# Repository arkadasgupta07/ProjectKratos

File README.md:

<p align="center">
  <!-- Replace the 'src' below with the actual path/link to your Project Kratos logo -->
  
</p>

<p align="center">
  <strong>~ Arka Dasgupta ~</strong><br>
  <strong>BITS Pilani, K. K. Birla Goa Campus</strong><br>
  <em>Aspiring to develop rovers by engineering their electronics, controls and automation subsystems.</em>
</p>

---

## ⚡ Core Engineering Domains

This repository primarily hosts my work in the domains of **Electronics, Controls and Automation**, aiming to build robust hardware and intelligent software stacks that drive our rovers across simulated and physical extraterrestrial terrains.

### 🔌 Electronics & Hardware
Focuses on the power, communication, and physical execution of the rover.
* **Power Distribution:** Custom-designed Power Distribution Boards (PDBs).
* **Embedded Systems:** Microcontroller programming and sensor integration.
* **Circuit Design:** Hardware schematics, PCB design, and component selection.
  
### 🤖 Automation & Controls
Focuses on making the rover intelligent and fully autonomous. 
* **Navigation Stack:** ROS/ROS2, Nav2, and SLAM for terrain mapping and path planning.
* **Computer Vision:** OpenCV and ArUCO marker detection for precise localization and object search.
* **Simulation:** Ground control stations and turtlebot/rover physics simulations in Gazebo.

---

## 📂 Repository Structure

Navigate through our project files below:

```text
ProjectKratos/
├── Documentation/            # Project reports, media, and track inductions
│   ├── Automation_Inductions/ # Automation track GUI, Nav2, and Vision demos
│   └── EnC_Inductions/        # Electronics & Communication documentation
├── Hardware/                 # PCB designs, schematics, and CAD files
├── src/                      # Robotics ROS packages & automation source code
└── README.md                 # You are here!

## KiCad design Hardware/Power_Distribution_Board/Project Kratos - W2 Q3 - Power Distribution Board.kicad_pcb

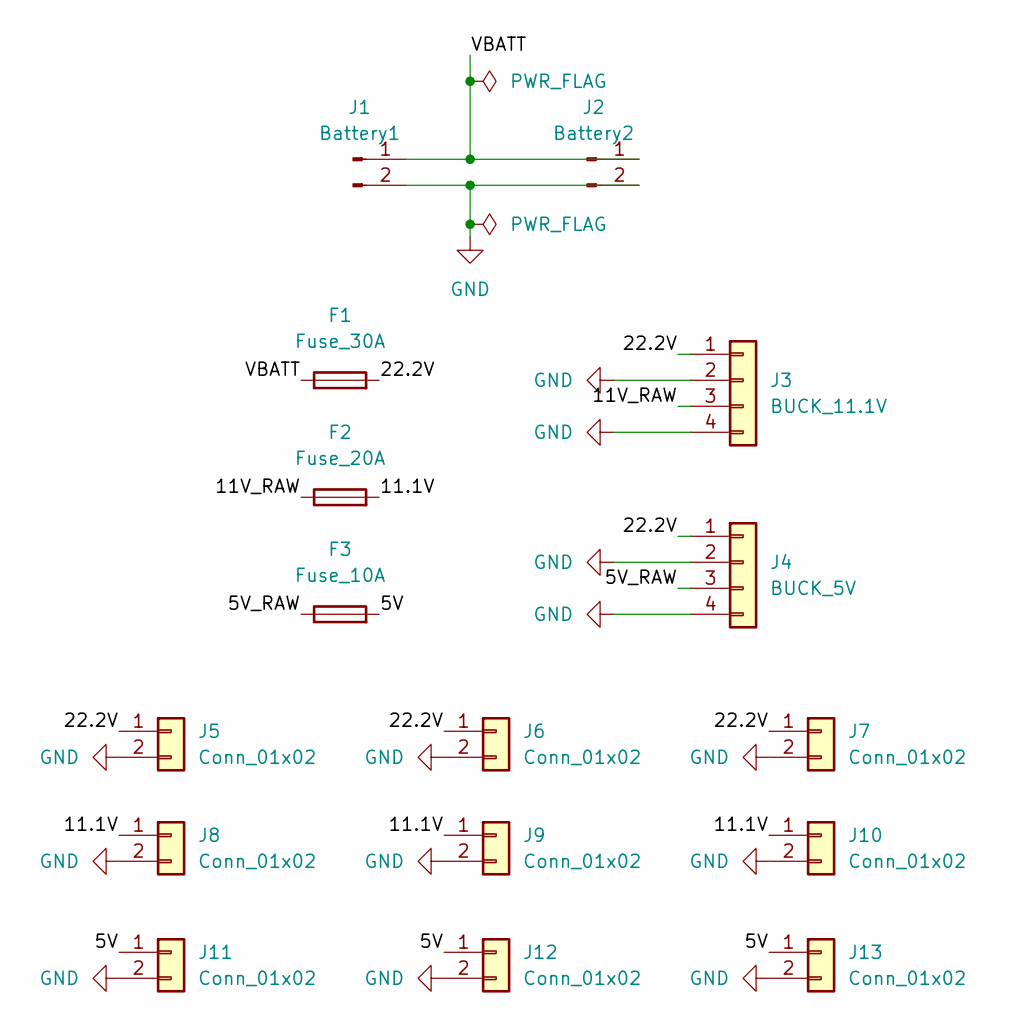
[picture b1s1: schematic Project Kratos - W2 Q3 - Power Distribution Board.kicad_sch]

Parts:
F1: Fuse_30A; FuseHolder_Blade_ATO_Littelfuse_FLR_178.6165
F2: Fuse_20A; FuseHolder_Blade_ATO_Littelfuse_FLR_178.6165
F3: Fuse_10A; FuseHolder_Blade_ATO_Littelfuse_FLR_178.6165
J1: Battery1; AMASS_XT60-F_1x02_P7.20mm_Vertical
J2: Battery2; AMASS_XT60-F_1x02_P7.20mm_Vertical
J3: BUCK_11.1V; PinHeader_1x04_P2.54mm_Vertical
J4: BUCK_5V; PinHeader_1x04_P2.54mm_Vertical
J5, J6, J7, J8, J9, J10: Conn_01x02; AMASS_XT60-M_1x02_P7.20mm_Vertical
J11, J12, J13: Conn_01x02; PinHeader_1x02_P2.54mm_Vertical

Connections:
/5V: F3.2, J11.1, J12.1, J13.1
/5V_RAW: F3.1, J4.3
/11.1V: F2.2, J8.1, J9.1, J10.1
/11V_RAW: F2.1, J3.3
/22.2V: F1.2, J3.1, J4.1, J5.1, J6.1, J7.1
/VBATT: F1.1, J1.1, J2.1
GND: J1.2, J2.2, J3.2, J3.4, J4.2, J4.4, J5.2, J6.2, J7.2, J8.2, J9.2, J10.2, J11.2, J12.2, J13.2

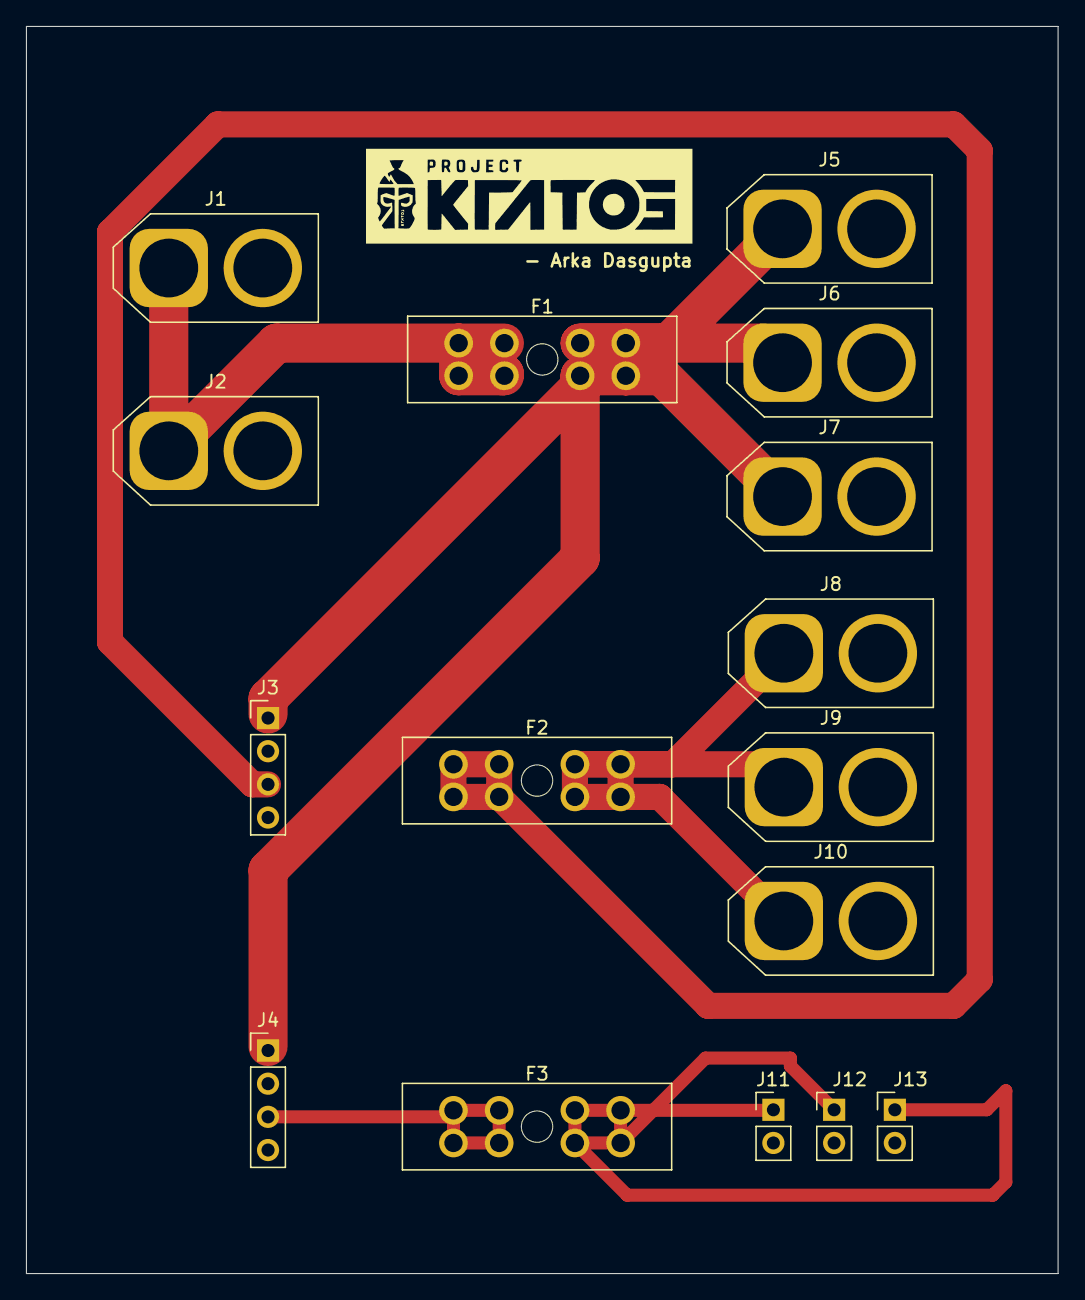
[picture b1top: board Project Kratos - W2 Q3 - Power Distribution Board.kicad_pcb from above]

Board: 2 copper layers, 79.0 x 95.5 mm, 16 parts (0 on the bottom side), 7 nets.

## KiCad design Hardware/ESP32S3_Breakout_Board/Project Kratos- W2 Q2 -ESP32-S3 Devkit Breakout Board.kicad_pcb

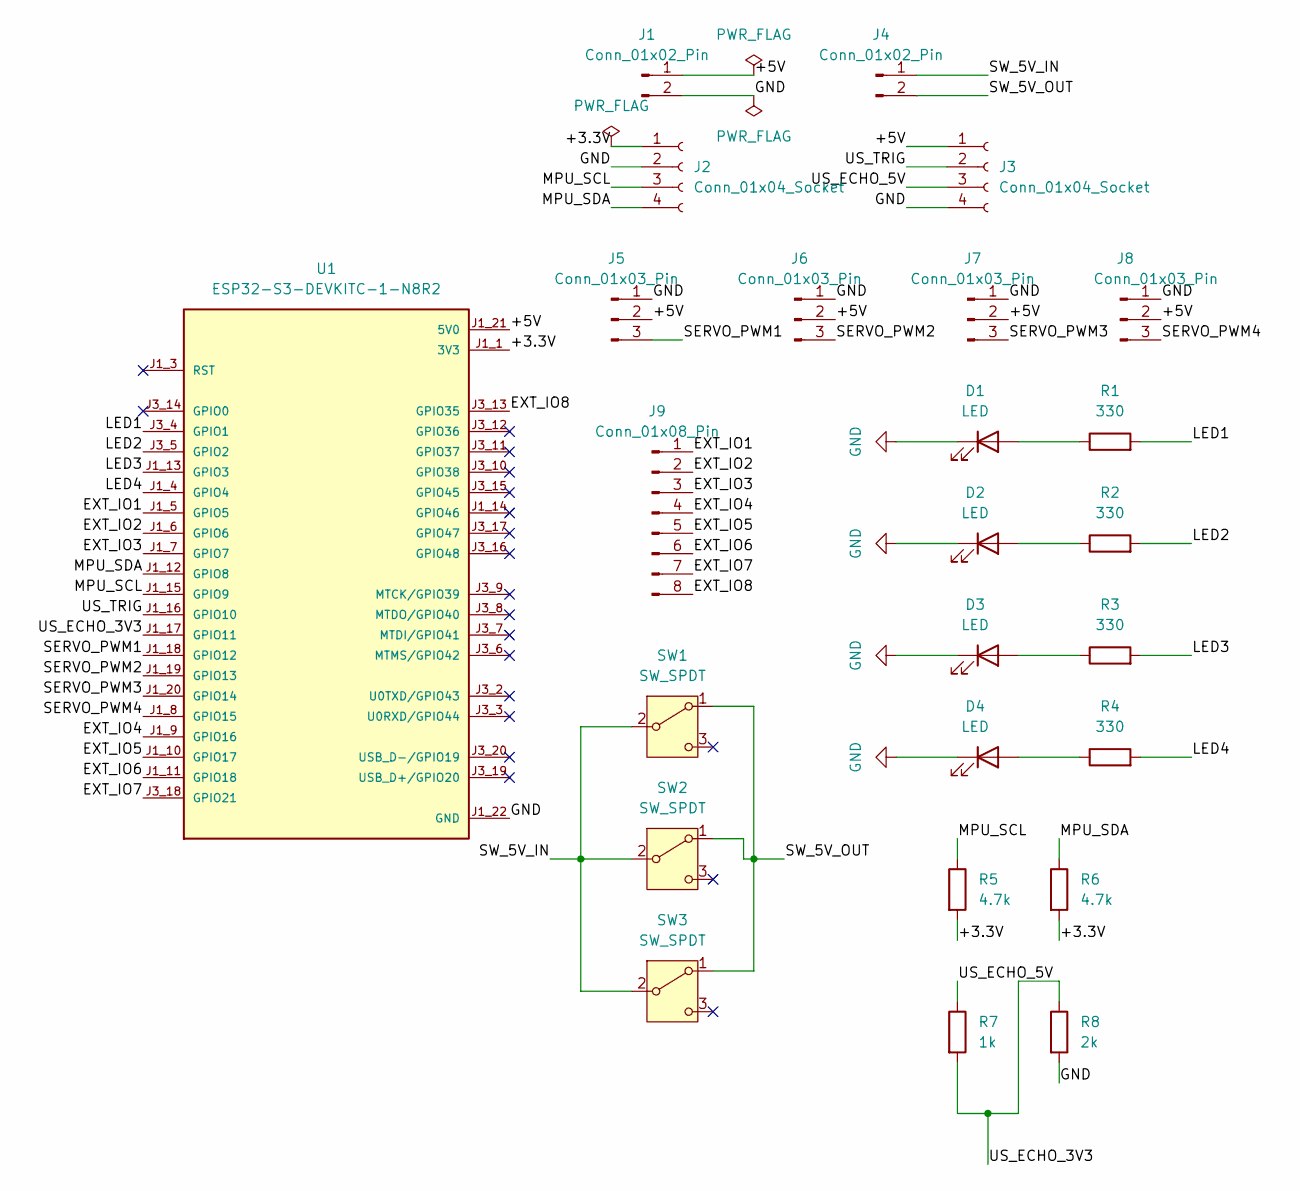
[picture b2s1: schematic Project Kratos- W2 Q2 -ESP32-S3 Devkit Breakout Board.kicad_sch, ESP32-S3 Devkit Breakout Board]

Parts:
D1, D2, D3, D4: LED; LED_D5.0mm
J1, J4: Conn_01x02_Pin; TerminalBlock_Phoenix_PT-1,5-2-3.5-H_1x02_P3.50mm_Horizontal
J2, J3: Conn_01x04_Socket; PinSocket_1x04_P2.54mm_Vertical
J5, J6, J7, J8: Conn_01x03_Pin; PinHeader_1x03_P2.54mm_Vertical
J9: Conn_01x08_Pin; PinHeader_1x08_P2.54mm_Vertical
R1, R2, R3, R4: 330; R_Axial_DIN0207_L6.3mm_D2.5mm_P7.62mm_Horizontal
R5, R6: 4.7k; R_Axial_DIN0207_L6.3mm_D2.5mm_P7.62mm_Horizontal
R7: 1k; R_Axial_DIN0207_L6.3mm_D2.5mm_P7.62mm_Horizontal
R8: 2k; R_Axial_DIN0207_L6.3mm_D2.5mm_P7.62mm_Horizontal
SW1, SW2, SW3: SW_SPDT; SW_Slide_SPDT_Straight_CK_OS102011MS2Q
U1: ESP32-S3-DEVKITC-1-N8R2; XCVR_ESP32-S3-DEVKITC-1-N8R2; PARTREV V1

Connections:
3V3: J2.1, R5.2, R6.2, U1.J1_1 (3V3), U1.J1_2 (3V3)
/+5V: J1.1, J3.1, J5.2, J6.2, J7.2, J8.2, U1.J1_21 (5V0)
/EXT_IO1: J9.1, U1.J1_5 (GPIO5)
/EXT_IO2: J9.2, U1.J1_6 (GPIO6)
/EXT_IO3: J9.3, U1.J1_7 (GPIO7)
/EXT_IO4: J9.4, U1.J1_9 (GPIO16)
/EXT_IO5: J9.5, U1.J1_10 (GPIO17)
/EXT_IO6: J9.6, U1.J1_11 (GPIO18)
/EXT_IO7: J9.7, U1.J3_18 (GPIO21)
/EXT_IO8: J9.8, U1.J3_13 (GPIO35)
/LED1: R1.2, U1.J3_4 (GPIO1)
/LED2: R2.2, U1.J3_5 (GPIO2)
/LED3: R3.2, U1.J1_13 (GPIO3)
/LED4: R4.2, U1.J1_4 (GPIO4)
/MPU_SCL: J2.3, R5.1, U1.J1_15 (GPIO9)
/MPU_SDA: J2.4, R6.1, U1.J1_12 (GPIO8)
/SERVO_PWM1: J5.3, U1.J1_18 (GPIO12)
/SERVO_PWM2: J6.3, U1.J1_19 (GPIO13)
/SERVO_PWM3: J7.3, U1.J1_20 (GPIO14)
/SERVO_PWM4: J8.3, U1.J1_8 (GPIO15)
/SW_5V_IN: J4.1, SW1.2 (B), SW2.2 (B), SW3.2 (B)
/SW_5V_OUT: J4.2, SW1.1 (A), SW2.1 (A), SW3.1 (A)
/US_ECHO_3V3: R7.2, R8.1, U1.J1_17 (GPIO11)
/US_ECHO_5V: J3.3, R7.1
/US_TRIG: J3.2, U1.J1_16 (GPIO10)
GND: D1.1 (K), D2.1 (K), D3.1 (K), D4.1 (K), J1.2, J2.2, J3.4, J5.1, J6.1, J7.1, J8.1, R8.2, U1.J1_22 (GND), U1.J3_1 (GND), U1.J3_21 (GND), U1.J3_22 (GND)
unnamed: D1.2 (A), R1.1
unnamed: D2.2 (A), R2.1
unnamed: D3.2 (A), R3.1
unnamed: D4.2 (A), R4.1

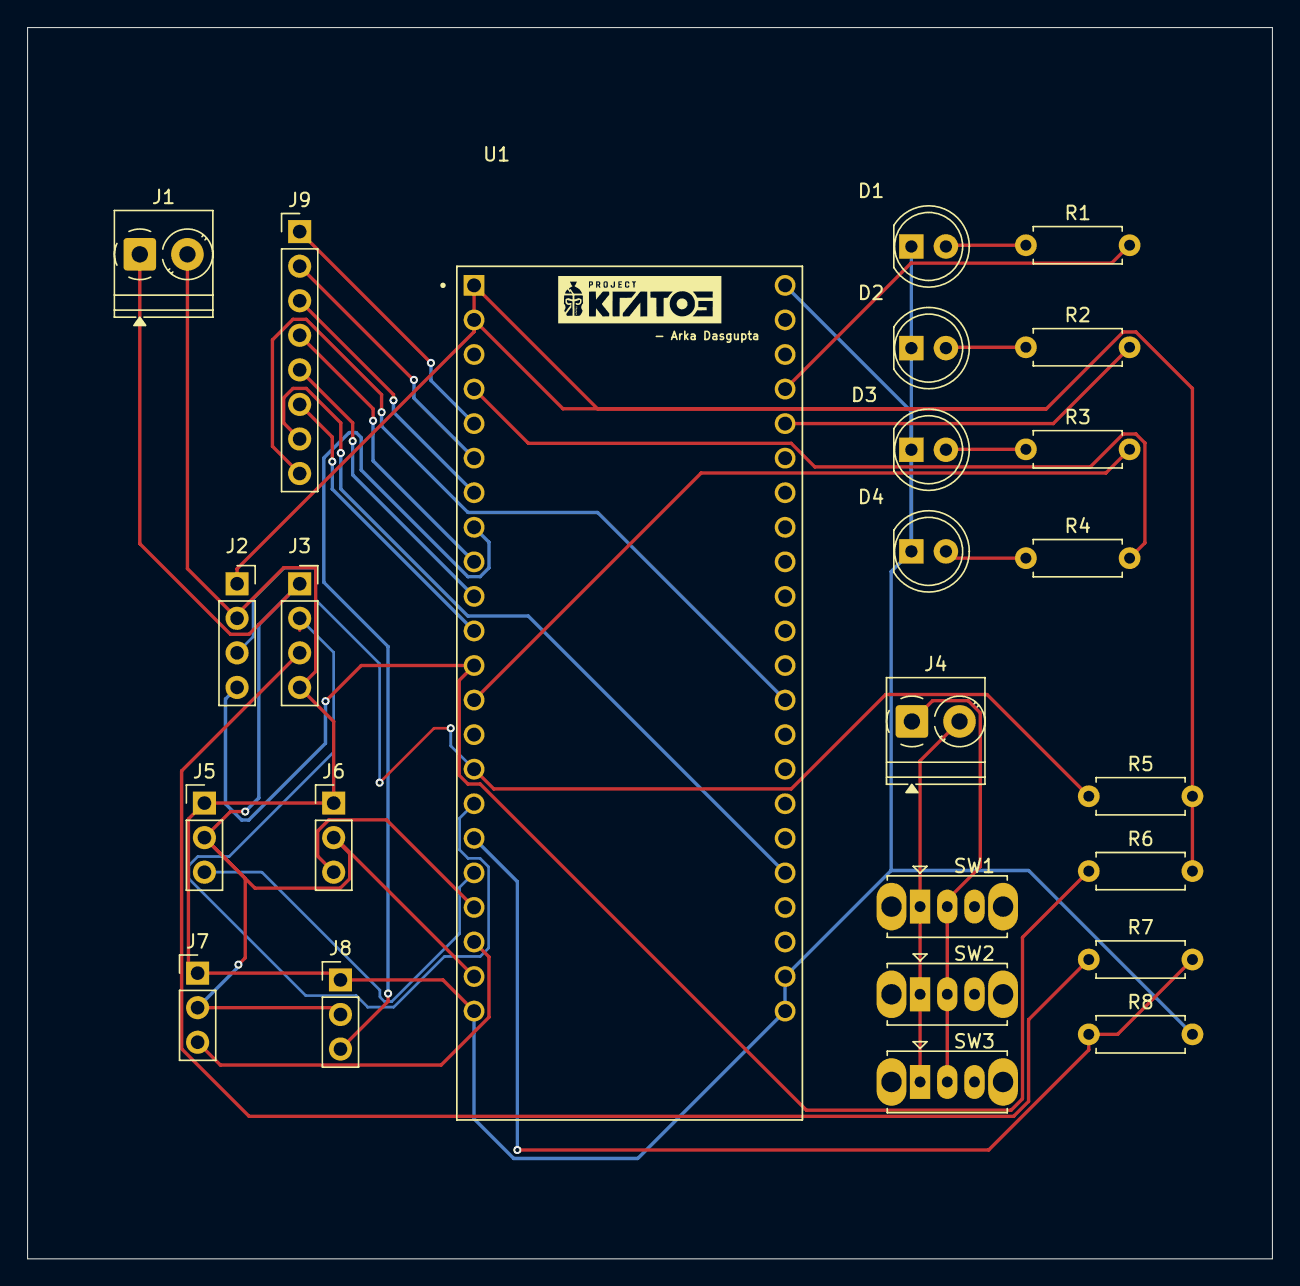
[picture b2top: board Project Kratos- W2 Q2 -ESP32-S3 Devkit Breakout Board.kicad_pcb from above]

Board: 2 copper layers, 91.5 x 90.5 mm, 25 parts (0 on the bottom side), 30 nets.

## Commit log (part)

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2026-06-21 Add ROS2 package structure without heavy local VS Code cache
2026-06-21 Update README with project and author details
    Added project details and author information to README.
2026-06-21 Upload submission screencast video
2026-06-29 Upload assignment code cleanly without massive cache files
